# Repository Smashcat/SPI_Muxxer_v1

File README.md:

# SPI_Muxxer_v1
8 Port ISP/SPI development and debugging board using ESP8266.

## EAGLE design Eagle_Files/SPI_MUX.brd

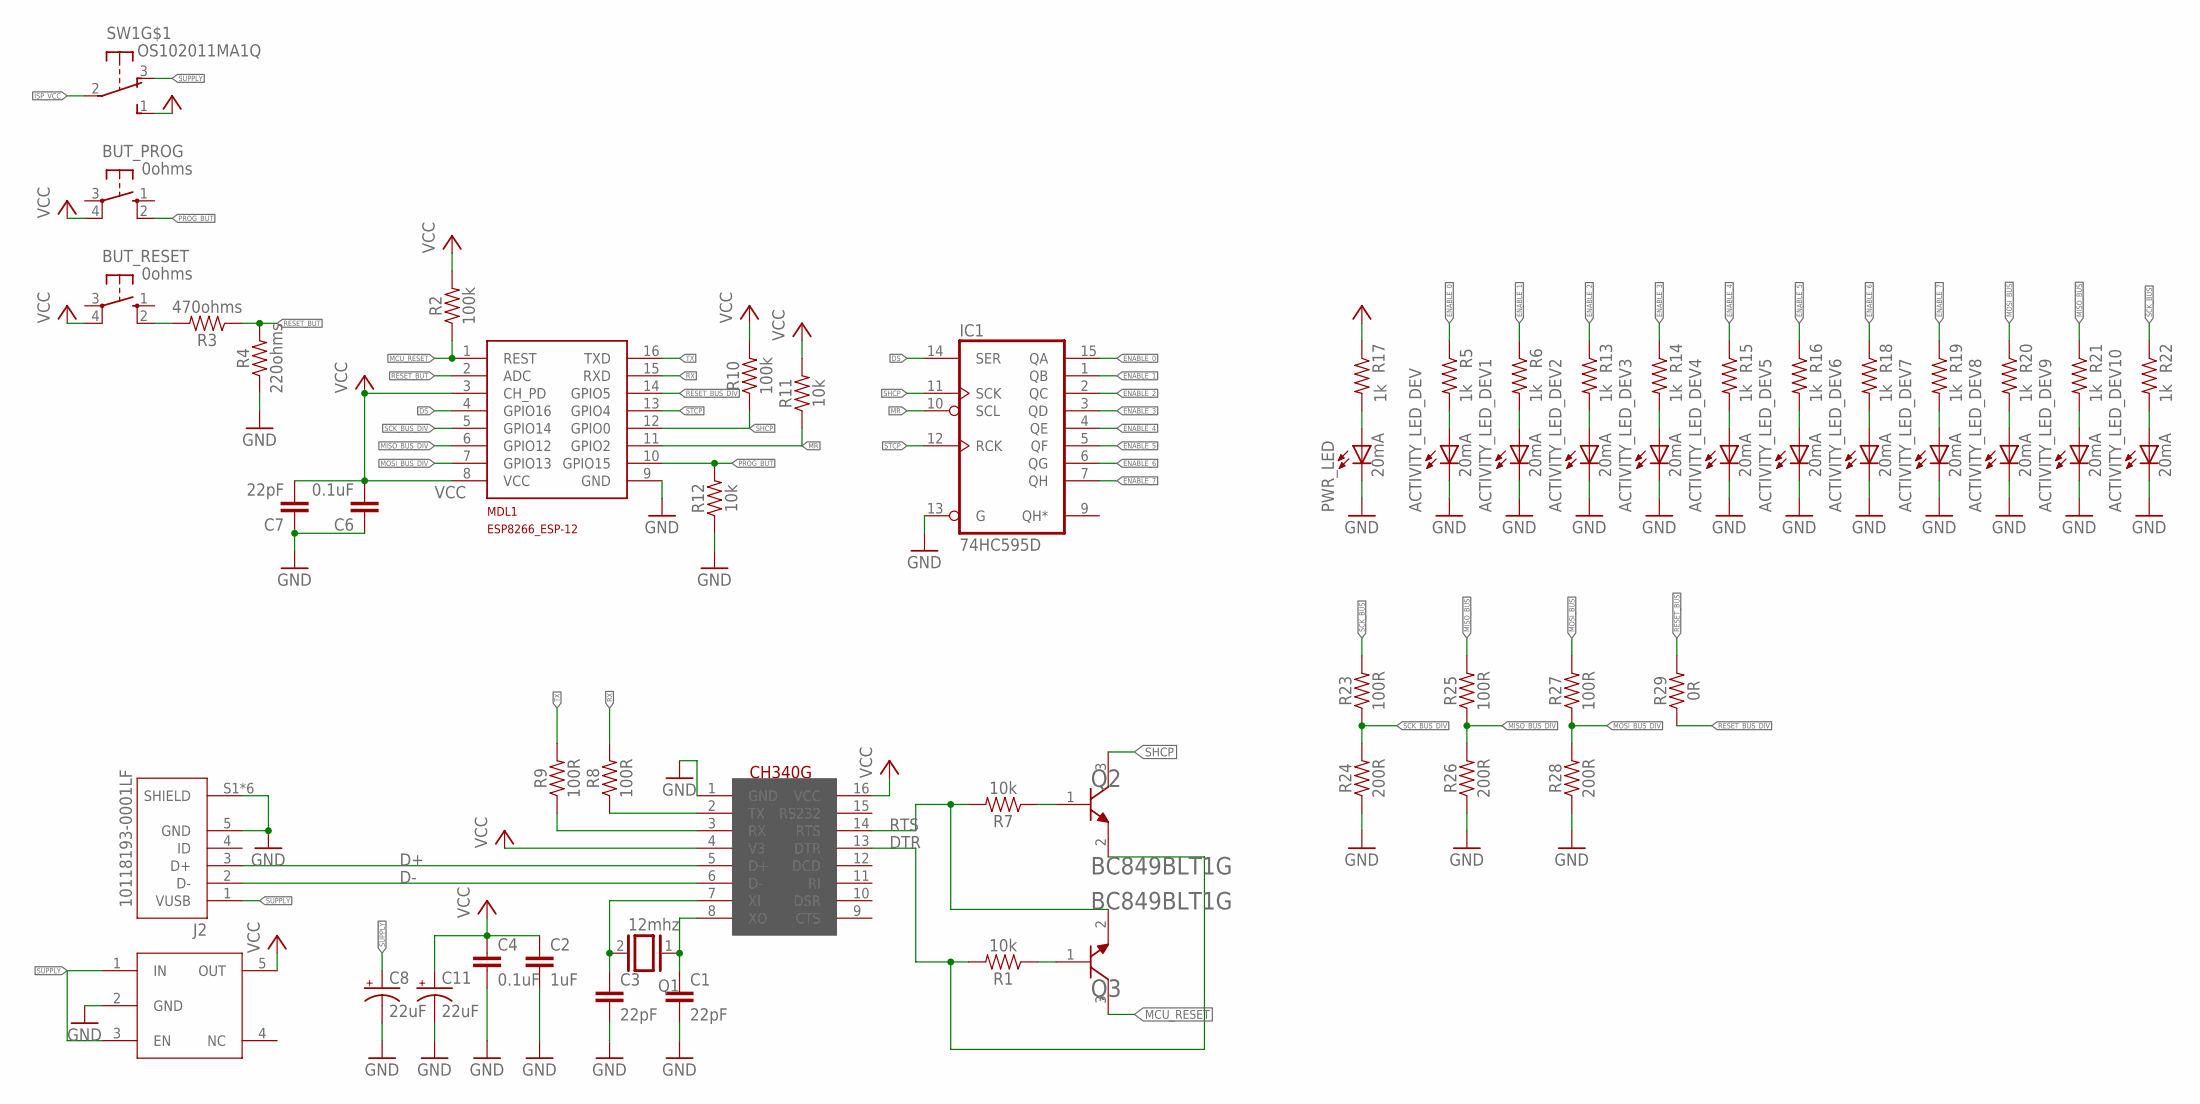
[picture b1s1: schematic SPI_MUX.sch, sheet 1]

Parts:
3V3_REGULATOR: 3v3 LDO; NCP718BSN330T1G
ACTIVITY_LED_DEV, ACTIVITY_LED_DEV1, ACTIVITY_LED_DEV2, ACTIVITY_LED_DEV3, ACTIVITY_LED_DEV4, ACTIVITY_LED_DEV5, ACTIVITY_LED_DEV6, ACTIVITY_LED_DEV7, ACTIVITY_LED_DEV8, ACTIVITY_LED_DEV9, ACTIVITY_LED_DEV10: 20mA; CHIP-LED0603
BUT_PROG: 0ohms; B3F-10XX
BUT_RESET: 0ohms; B3F-10XX
C1, C3, C7: 22pF; C0603
C2: 1uF; C0603
C4, C6: 0.1uF; C0603
C8, C11: 22uF; PANASONIC_C
IC1: 74HC595D; SO16
J2: 10118193-0001LF; FCI_10118193-0001LF
MDL1: MCU; ESP8266-ESP12
PWR_LED: 20mA; CHIP-LED0603
Q1: 12mhz; QS
Q2, Q3: ON_SEMICONDUCTOR_BC849BLT1GON_SEMICONDUCTOR_BC849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; ON_SEMICONDUCTOR_BC849BLT1G_0
R1, R7, R11, R12: 10k; 0603
R2, R10: 100k; 0603
R3: 470ohms; 0603
R4: 220ohms; 0603
R5, R6, R13, R14, R15, R16, R17, R18, R19, R20, R21, R22: 1k; 0603
R8, R9, R23, R25, R27: 100R; 0603
R24, R26, R28: 200R; 0603
R29: 0R; 0603
SW1: OS102011MA1Q
U$1: CH340G; SOIC16

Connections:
ACTIVITY: ACTIVITY_LED_DEV.A, R5.2
ACTIVITY1: ACTIVITY_LED_DEV1.A, R6.2
ACTIVITY2: ACTIVITY_LED_DEV2.A, R13.2
ACTIVITY3: ACTIVITY_LED_DEV3.A, R14.2
ACTIVITY4: ACTIVITY_LED_DEV4.A, R15.2
ACTIVITY5: ACTIVITY_LED_DEV5.A, R16.2
ACTIVITY6: ACTIVITY_LED_DEV6.A, R18.2
ACTIVITY7: ACTIVITY_LED_DEV7.A, R19.2
ACTIVITY8: ACTIVITY_LED_DEV8.A, R20.2
ACTIVITY9: ACTIVITY_LED_DEV9.A, R21.2
ACTIVITY10: ACTIVITY_LED_DEV10.A, R22.2
CRYSTALIN: C3.1, Q1.2, U$1.7 (XI)
CRYSTALOUT: C1.1, Q1.1, U$1.8 (XO)
D+: J2.3 (D+), U$1.5 (D+)
D-: J2.2 (D-), U$1.6 (D-)
DS: IC1.14 (SER), MDL1.4 (GPIO16)
DTR: Q2.2 (E), R1.2, U$1.13 (DTR)
ENABLE_0: IC1.15 (QA), R5.1; also elsewhere on the board
ENABLE_1: IC1.1 (QB), R6.1; also elsewhere on the board
ENABLE_2: IC1.2 (QC), R13.1; also elsewhere on the board
ENABLE_3: IC1.3 (QD), R14.1; also elsewhere on the board
ENABLE_4: IC1.4 (QE), R15.1; also elsewhere on the board
ENABLE_5: IC1.5 (QF), R16.1; also elsewhere on the board
ENABLE_6: IC1.6 (QG), R18.1; also elsewhere on the board
ENABLE_7: IC1.7 (QH), R19.1; also elsewhere on the board
GND: 3V3_REGULATOR.2 (GND), ACTIVITY_LED_DEV.C, ACTIVITY_LED_DEV1.C, ACTIVITY_LED_DEV2.C, ACTIVITY_LED_DEV3.C, ACTIVITY_LED_DEV4.C, ACTIVITY_LED_DEV5.C, ACTIVITY_LED_DEV6.C, ACTIVITY_LED_DEV7.C, ACTIVITY_LED_DEV8.C, ACTIVITY_LED_DEV9.C, ACTIVITY_LED_DEV10.C, C1.2, C2.2, C3.2, C4.2, C6.1, C7.1, C8.-, C11.-, IC1.8 (GND), IC1.13 (G), J2.5 (GND), J2.S1 (SHIELD), J2.S2 (SHIELD), J2.S3 (SHIELD), J2.S4 (SHIELD), J2.S5 (SHIELD), J2.S6 (SHIELD), MDL1.9 (GND), PWR_LED.C, R4.1, R12.1, R24.1, R26.1, R28.1, U$1.1 (GND); also elsewhere on the board
ISP_VCC: SW1.2; also elsewhere on the board
MCU_RESET: MDL1.1 (REST), Q3.3 (C), R2.1
MISO_BUS: R21.1, R25.2; also elsewhere on the board
MISO_BUS_DIV: MDL1.6 (GPIO12), R25.1, R26.2
MOSI_BUS: R20.1, R27.2; also elsewhere on the board
MOSI_BUS_DIV: MDL1.7 (GPIO13), R27.1, R28.2
MR: IC1.10 (SCL), MDL1.11 (GPIO2), R11.1
unnamed: BUT_RESET.2 (S1), R3.2
unnamed: Q3.1 (B), R1.1
unnamed: Q2.1 (B), R7.1
PROG_BUT: BUT_PROG.2 (S1), MDL1.10 (GPIO15), R12.2
PWR_RES: PWR_LED.A, R17.2
RESET_BUS: R29.2; also elsewhere on the board
RESET_BUS_DIV: MDL1.14 (GPIO5), R29.1
RESET_BUT: MDL1.2 (ADC), R3.1, R4.2
RTS: Q3.2 (E), R7.2, U$1.14 (RTS)
RX: MDL1.15 (RXD), R8.2
SCK_BUS: R22.1, R23.2; also elsewhere on the board
SCK_BUS_DIV: MDL1.5 (GPIO14), R23.1, R24.2
SHCP: IC1.11 (SCK), MDL1.12 (GPIO0), Q2.3 (C), R10.1
STCP: IC1.12 (RCK), MDL1.13 (GPIO4)
SUPPLY: 3V3_REGULATOR.1 (IN), 3V3_REGULATOR.3 (EN), C8.+, J2.1 (VUSB), SW1.3 (O)
TX: MDL1.16 (TXD), R9.2
TXFROMMCU: R9.1, U$1.3 (RX)
TXFROMPROGRAMMER: R8.1, U$1.2 (TX)
VCC: 3V3_REGULATOR.5 (OUT), BUT_PROG.4 (P1), BUT_RESET.4 (P1), C2.1, C4.1, C6.2, C7.2, C11.+, IC1.16 (VCC), MDL1.3 (CH_PD), MDL1.8 (VCC), R2.2, R10.2, R11.2, R17.1, SW1.1 (S), U$1.4 (V3), U$1.16 (VCC); also elsewhere on the board

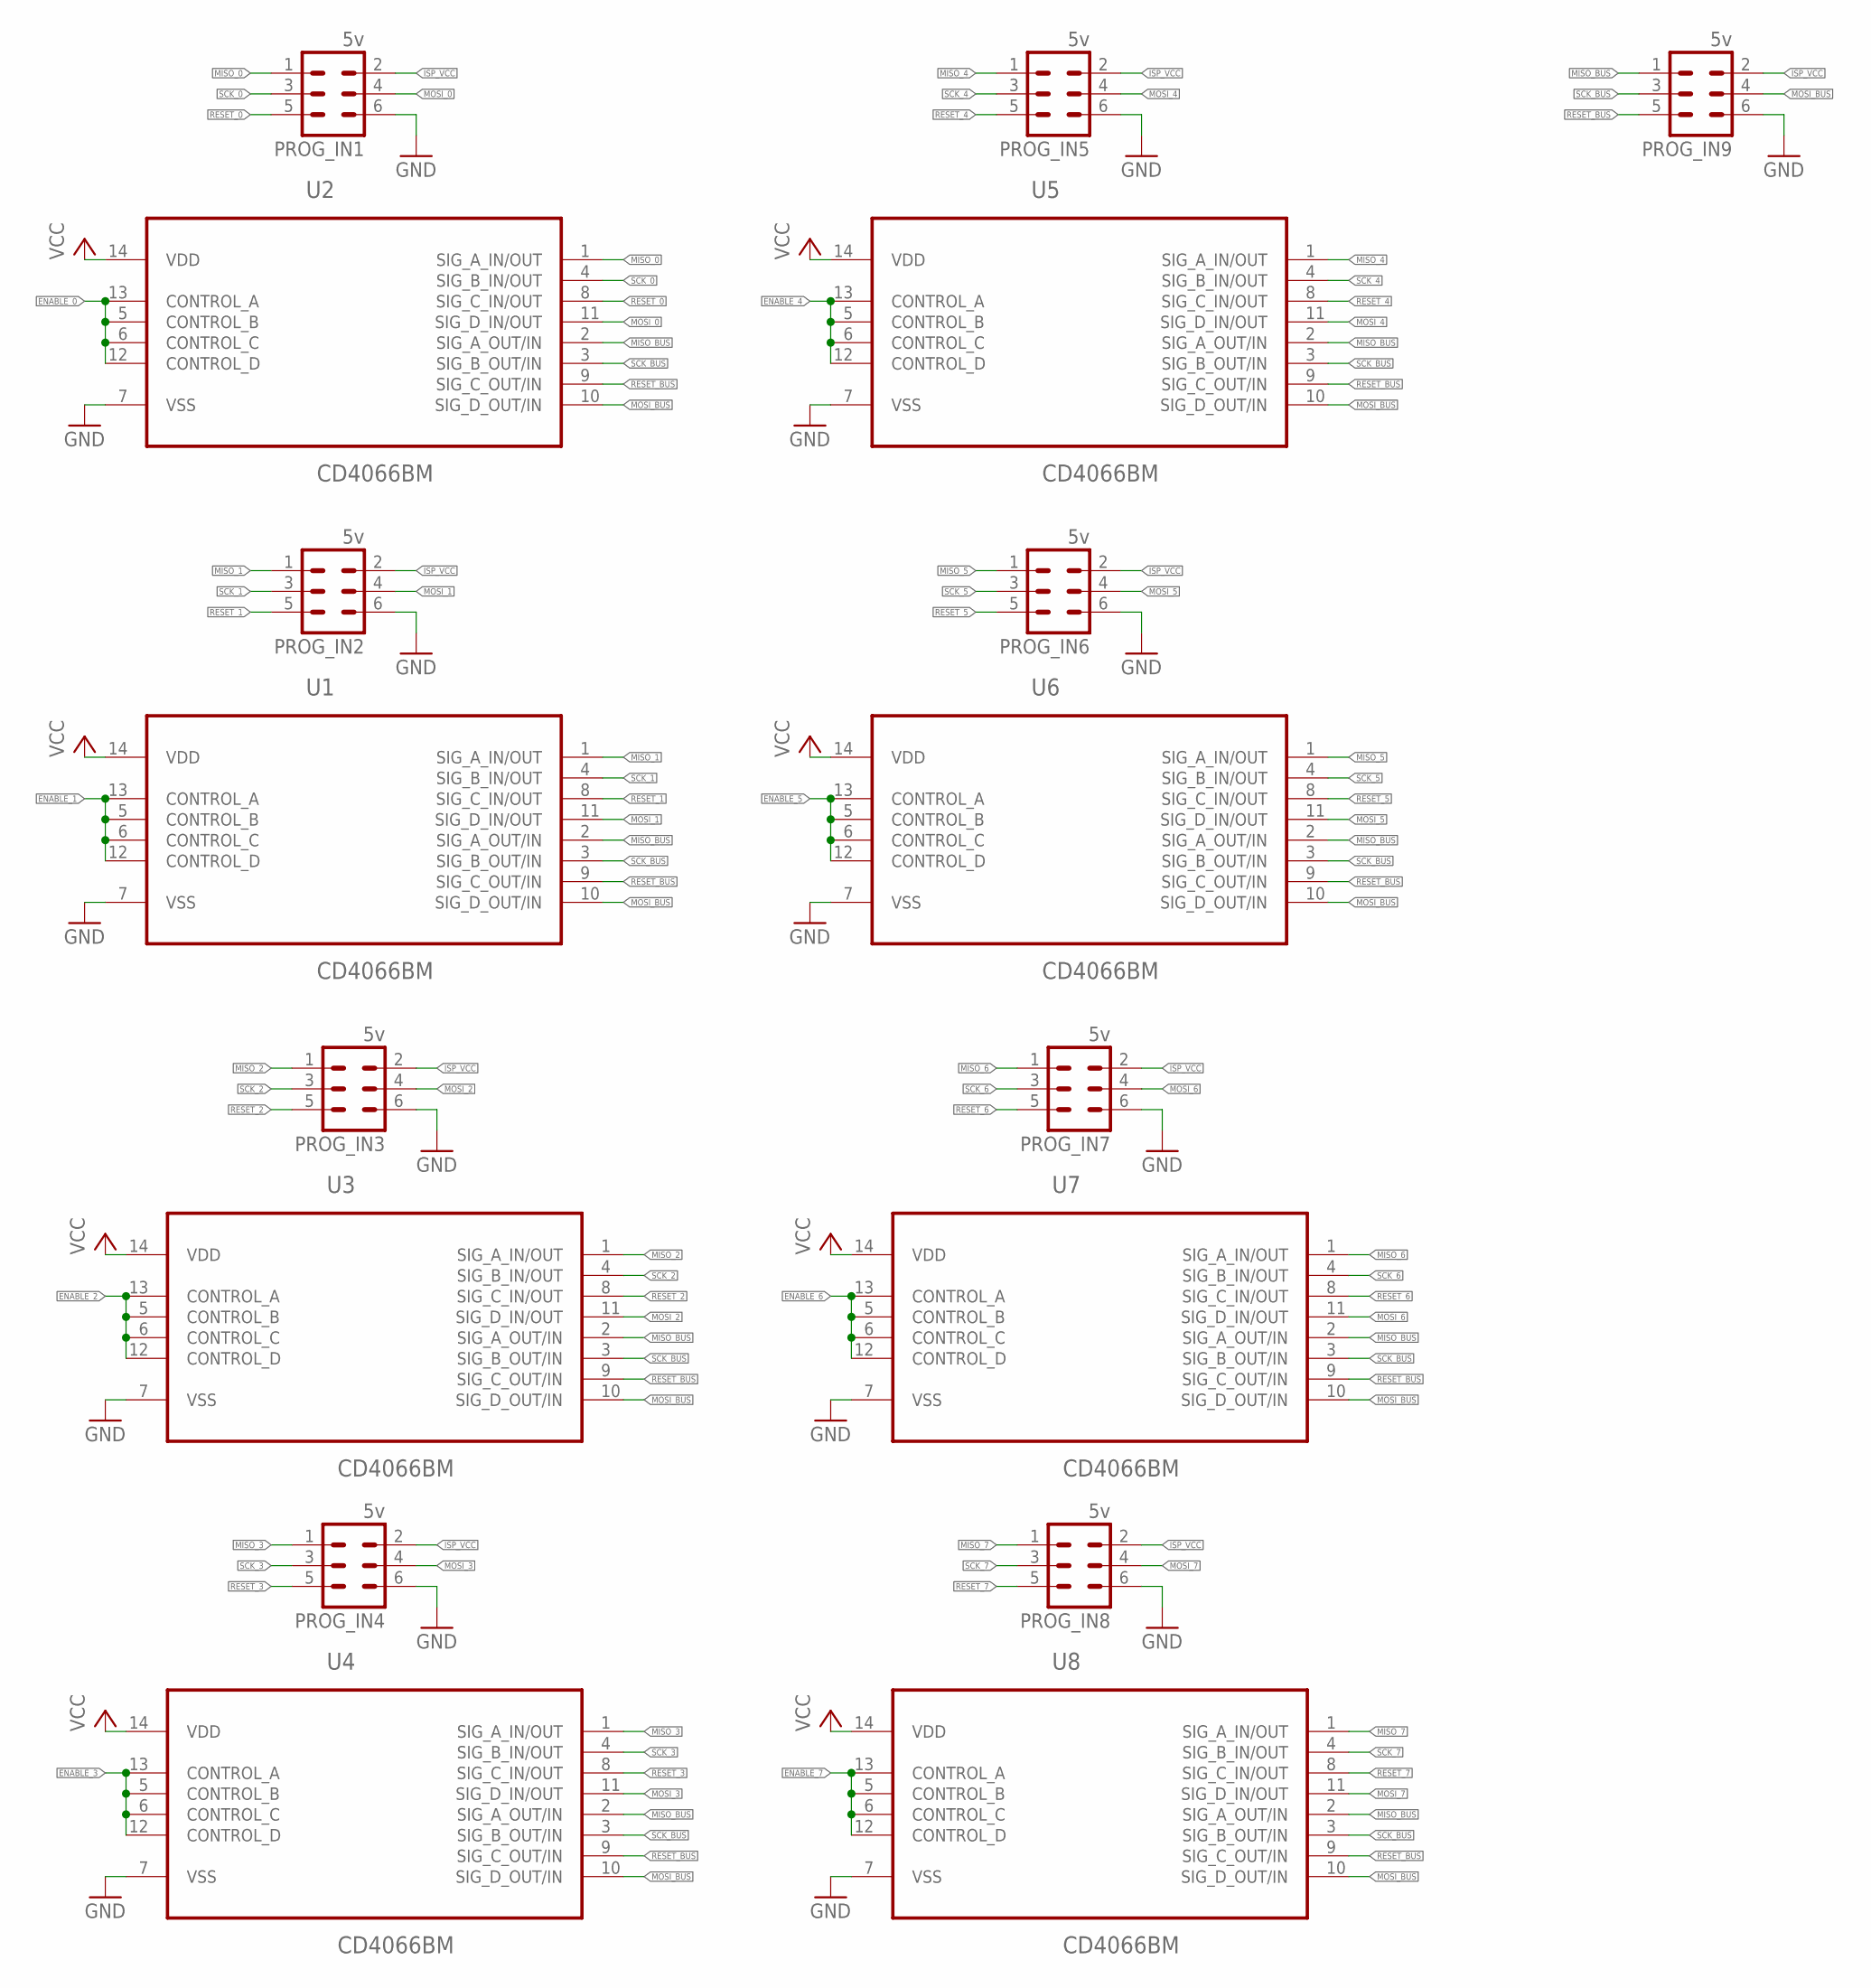
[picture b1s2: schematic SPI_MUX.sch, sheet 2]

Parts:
PROG_IN1, PROG_IN2, PROG_IN3, PROG_IN4, PROG_IN5, PROG_IN6, PROG_IN7, PROG_IN8, PROG_IN9: 5v; MA03-2
U1, U2, U3, U4, U5, U6, U7, U8: CD4066BM; SOIC127P600X175-14N

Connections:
ENABLE_0: U2.5 (CONTROL_B), U2.6 (CONTROL_C), U2.12 (CONTROL_D), U2.13 (CONTROL_A); also elsewhere on the board
ENABLE_1: U1.5 (CONTROL_B), U1.6 (CONTROL_C), U1.12 (CONTROL_D), U1.13 (CONTROL_A); also elsewhere on the board
ENABLE_2: U3.5 (CONTROL_B), U3.6 (CONTROL_C), U3.12 (CONTROL_D), U3.13 (CONTROL_A); also elsewhere on the board
ENABLE_3: U4.5 (CONTROL_B), U4.6 (CONTROL_C), U4.12 (CONTROL_D), U4.13 (CONTROL_A); also elsewhere on the board
ENABLE_4: U5.5 (CONTROL_B), U5.6 (CONTROL_C), U5.12 (CONTROL_D), U5.13 (CONTROL_A); also elsewhere on the board
ENABLE_5: U6.5 (CONTROL_B), U6.6 (CONTROL_C), U6.12 (CONTROL_D), U6.13 (CONTROL_A); also elsewhere on the board
ENABLE_6: U7.5 (CONTROL_B), U7.6 (CONTROL_C), U7.12 (CONTROL_D), U7.13 (CONTROL_A); also elsewhere on the board
ENABLE_7: U8.5 (CONTROL_B), U8.6 (CONTROL_C), U8.12 (CONTROL_D), U8.13 (CONTROL_A); also elsewhere on the board
GND: PROG_IN1.6, PROG_IN2.6, PROG_IN3.6, PROG_IN4.6, PROG_IN5.6, PROG_IN6.6, PROG_IN7.6, PROG_IN8.6, PROG_IN9.6, U1.7 (VSS), U2.7 (VSS), U3.7 (VSS), U4.7 (VSS), U5.7 (VSS), U6.7 (VSS), U7.7 (VSS), U8.7 (VSS); also elsewhere on the board
ISP_VCC: PROG_IN1.2, PROG_IN2.2, PROG_IN3.2, PROG_IN4.2, PROG_IN5.2, PROG_IN6.2, PROG_IN7.2, PROG_IN8.2, PROG_IN9.2; also elsewhere on the board
MISO_0: PROG_IN1.1, U2.1 (SIG_A_IN/OUT)
MISO_1: PROG_IN2.1, U1.1 (SIG_A_IN/OUT)
MISO_2: PROG_IN3.1, U3.1 (SIG_A_IN/OUT)
MISO_3: PROG_IN4.1, U4.1 (SIG_A_IN/OUT)
MISO_4: PROG_IN5.1, U5.1 (SIG_A_IN/OUT)
MISO_5: PROG_IN6.1, U6.1 (SIG_A_IN/OUT)
MISO_6: PROG_IN7.1, U7.1 (SIG_A_IN/OUT)
MISO_7: PROG_IN8.1, U8.1 (SIG_A_IN/OUT)
MISO_BUS: PROG_IN9.1, U1.2 (SIG_A_OUT/IN), U2.2 (SIG_A_OUT/IN), U3.2 (SIG_A_OUT/IN), U4.2 (SIG_A_OUT/IN), U5.2 (SIG_A_OUT/IN), U6.2 (SIG_A_OUT/IN), U7.2 (SIG_A_OUT/IN), U8.2 (SIG_A_OUT/IN); also elsewhere on the board
MOSI_0: PROG_IN1.4, U2.11 (SIG_D_IN/OUT)
MOSI_1: PROG_IN2.4, U1.11 (SIG_D_IN/OUT)
MOSI_2: PROG_IN3.4, U3.11 (SIG_D_IN/OUT)
MOSI_3: PROG_IN4.4, U4.11 (SIG_D_IN/OUT)
MOSI_4: PROG_IN5.4, U5.11 (SIG_D_IN/OUT)
MOSI_5: PROG_IN6.4, U6.11 (SIG_D_IN/OUT)
MOSI_6: PROG_IN7.4, U7.11 (SIG_D_IN/OUT)
MOSI_7: PROG_IN8.4, U8.11 (SIG_D_IN/OUT)
MOSI_BUS: PROG_IN9.4, U1.10 (SIG_D_OUT/IN), U2.10 (SIG_D_OUT/IN), U3.10 (SIG_D_OUT/IN), U4.10 (SIG_D_OUT/IN), U5.10 (SIG_D_OUT/IN), U6.10 (SIG_D_OUT/IN), U7.10 (SIG_D_OUT/IN), U8.10 (SIG_D_OUT/IN); also elsewhere on the board
RESET_0: PROG_IN1.5, U2.8 (SIG_C_IN/OUT)
RESET_1: PROG_IN2.5, U1.8 (SIG_C_IN/OUT)
RESET_2: PROG_IN3.5, U3.8 (SIG_C_IN/OUT)
RESET_3: PROG_IN4.5, U4.8 (SIG_C_IN/OUT)
RESET_4: PROG_IN5.5, U5.8 (SIG_C_IN/OUT)
RESET_5: PROG_IN6.5, U6.8 (SIG_C_IN/OUT)
RESET_6: PROG_IN7.5, U7.8 (SIG_C_IN/OUT)
RESET_7: PROG_IN8.5, U8.8 (SIG_C_IN/OUT)
RESET_BUS: PROG_IN9.5, U1.9 (SIG_C_OUT/IN), U2.9 (SIG_C_OUT/IN), U3.9 (SIG_C_OUT/IN), U4.9 (SIG_C_OUT/IN), U5.9 (SIG_C_OUT/IN), U6.9 (SIG_C_OUT/IN), U7.9 (SIG_C_OUT/IN), U8.9 (SIG_C_OUT/IN); also elsewhere on the board
SCK_0: PROG_IN1.3, U2.4 (SIG_B_IN/OUT)
SCK_1: PROG_IN2.3, U1.4 (SIG_B_IN/OUT)
SCK_2: PROG_IN3.3, U3.4 (SIG_B_IN/OUT)
SCK_3: PROG_IN4.3, U4.4 (SIG_B_IN/OUT)
SCK_4: PROG_IN5.3, U5.4 (SIG_B_IN/OUT)
SCK_5: PROG_IN6.3, U6.4 (SIG_B_IN/OUT)
SCK_6: PROG_IN7.3, U7.4 (SIG_B_IN/OUT)
SCK_7: PROG_IN8.3, U8.4 (SIG_B_IN/OUT)
SCK_BUS: PROG_IN9.3, U1.3 (SIG_B_OUT/IN), U2.3 (SIG_B_OUT/IN), U3.3 (SIG_B_OUT/IN), U4.3 (SIG_B_OUT/IN), U5.3 (SIG_B_OUT/IN), U6.3 (SIG_B_OUT/IN), U7.3 (SIG_B_OUT/IN), U8.3 (SIG_B_OUT/IN); also elsewhere on the board
VCC: U1.14 (VDD), U2.14 (VDD), U3.14 (VDD), U4.14 (VDD), U5.14 (VDD), U6.14 (VDD), U7.14 (VDD), U8.14 (VDD); also elsewhere on the board

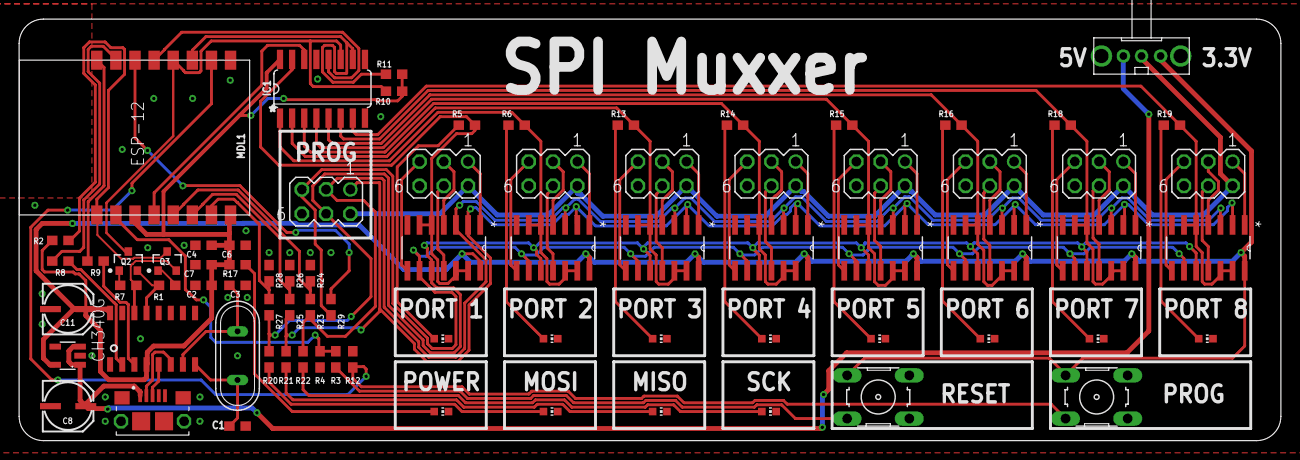
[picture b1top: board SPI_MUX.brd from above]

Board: 2 copper layers, 132.1 x 44.1 mm, 77 parts (0 on the bottom side), 84 nets.

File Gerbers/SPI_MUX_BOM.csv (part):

"Part";"Value";"Device";"Package";"Description";"AVAILABILITY";"CIIVA_IDS";"COMPONENT_LINK_1_DESCRIPTION";"COMPONENT_LINK_1_URL";"COMPONENT_LINK_3_DESCRIPTION";"COMPONENT_LINK_3_URL";"DATASHEET";"DATASHEET_VERSION";"DESCRIPTION";"FOOTPRINT_VARIANT_NAME_0";"FT_MIN_MHZ";"IC_CONTINUOUS_A";"IMPORTED";"IMPORTED_FROM";"IMPORT_TS";"MF";"MOUNTING_TECHNOLOGY";"MP";"MPN";"OC_FARNELL";"OC_NEWARK";"PACKAGE";"PACKAGE_DESCRIPTION";"PACKAGE_VERSION";"PACKING";"POLARITY";"PREFIX";"PRICE";"PROD_ID";"RELEASE_DATE";"ROHS";"SPICEPREFIX";"SUPPLIER";"VALUE";"VAULT_GUID";"VAULT_REVISION";
"3V3_REGULATOR";"3v3 LDO";"NCP718BSN330T1G";"NCP718BSN330T1G";"";"";"";"";"";"";"";"";"";"";"";"";"";"";"";"";"";"";"";"";"";"";"";"";"";"";"";"";"";"";"";"";"";"";"";"";"";
"ACTIVITY_LED_DEV";"20mA";"LEDCHIP-LED0603";"CHIP-LED0603";"LED";"";"";"";"";"";"";"";"";"";"";"";"";"";"";"";"";"";"";"";"";"";"";"";"";"";"";"";"";"";"";"";"";"";"";"";"";
"ACTIVITY_LED_DEV1";"20mA";"LEDCHIP-LED0603";"CHIP-LED0603";"LED";"";"";"";"";"";"";"";"";"";"";"";"";"";"";"";"";"";"";"";"";"";"";"";"";"";"";"";"";"";"";"";"";"";"";"";"";
"ACTIVITY_LED_DEV2";"20mA";"LEDCHIP-LED0603";"CHIP-LED0603";"LED";"";"";"";"";"";"";"";"";"";"";"";"";"";"";"";"";"";"";"";"";"";"";"";"";"";"";"";"";"";"";"";"";"";"";"";"";
"ACTIVITY_LED_DEV3";"20mA";"LEDCHIP-LED0603";"CHIP-LED0603";"LED";"";"";"";"";"";"";"";"";"";"";"";"";"";"";"";"";"";"";"";"";"";"";"";"";"";"";"";"";"";"";"";"";"";"";"";"";
"ACTIVITY_LED_DEV4";"20mA";"LEDCHIP-LED0603";"CHIP-LED0603";"LED";"";"";"";"";"";"";"";"";"";"";"";"";"";"";"";"";"";"";"";"";"";"";"";"";"";"";"";"";"";"";"";"";"";"";"";"";
"ACTIVITY_LED_DEV5";"20mA";"LEDCHIP-LED0603";"CHIP-LED0603";"LED";"";"";"";"";"";"";"";"";"";"";"";"";"";"";"";"";"";"";"";"";"";"";"";"";"";"";"";"";"";"";"";"";"";"";"";"";
"ACTIVITY_LED_DEV6";"20mA";"LEDCHIP-LED0603";"CHIP-LED0603";"LED";"";"";"";"";"";"";"";"";"";"";"";"";"";"";"";"";"";"";"";"";"";"";"";"";"";"";"";"";"";"";"";"";"";"";"";"";
"ACTIVITY_LED_DEV7";"20mA";"LEDCHIP-LED0603";"CHIP-LED0603";"LED";"";"";"";"";"";"";"";"";"";"";"";"";"";"";"";"";"";"";"";"";"";"";"";"";"";"";"";"";"";"";"";"";"";"";"";"";
"ACTIVITY_LED_DEV8";"20mA";"LEDCHIP-LED0603";"CHIP-LED0603";"LED";"";"";"";"";"";"";"";"";"";"";"";"";"";"";"";"";"";"";"";"";"";"";"";"";"";"";"";"";"";"";"";"";"";"";"";"";
"ACTIVITY_LED_DEV9";"20mA";"LEDCHIP-LED0603";"CHIP-LED0603";"LED";"";"";"";"";"";"";"";"";"";"";"";"";"";"";"";"";"";"";"";"";"";"";"";"";"";"";"";"";"";"";"";"";"";"";"";"";
"ACTIVITY_LED_DEV10";"20mA";"LEDCHIP-LED0603";"CHIP-LED0603";"LED";"";"";"";"";"";"";"";"";"";"";"";"";"";"";"";"";"";"";"";"";"";"";"";"";"";"";"";"";"";"";"";"";"";"";"";"";
"BUT_PROG";"0ohms";"10-XX";"B3F-10XX";"OMRON SWITCH";"";"";"";"";"";"";"";"";"";"";"";"";"";"";"";"";"";"";"B3F-1000";"176432";"36M3542";"";"";"";"";"";"";"";"";"";"";"";"";"";"";"";
"BUT_RESET";"0ohms";"10-XX";"B3F-10XX";"OMRON SWITCH";"";"";"";"";"";"";"";"";"";"";"";"";"";"";"";"";"";"";"B3F-1000";"176432";"36M3542";"";"";"";"";"";"";"";"";"";"";"";"";"";"";"";
"C1";"22pF";"C-EUC0603";"C0603";"CAPACITOR, European symbol";"";"";"";"";"";"";"";"";"";"";"";"";"";"";"";"";"";"";"";"";"";"";"";"";"";"";"";"";"";"";"";"C";"";"";"";"";
"C2";"1uF";"C-EUC0603";"C0603";"CAPACITOR, European symbol";"";"";"";"";"";"";"";"";"";"";"";"";"";"";"";"";"";"";"";"";"";"";"";"";"";"";"";"";"";"";"";"C";"";"";"";"";
"C3";"22pF";"C-EUC0603";"C0603";"CAPACITOR, European symbol";"";"";"";"";"";"";"";"";"";"";"";"";"";"";"";"";"";"";"";"";"";"";"";"";"";"";"";"";"";"";"";"C";"";"";"";"";
"C4";"0.1uF";"C-EUC0603";"C0603";"CAPACITOR, European symbol";"";"";"";"";"";"";"";"";"";"";"";"";"";"";"";"";"";"";"";"";"";"";"";"";"";"";"";"";"";"";"";"C";"";"";"";"";
"C6";"0.1uF";"C-EUC0603";"C0603";"CAPACITOR, European symbol";"";"";"";"";"";"";"";"";"";"";"";"";"";"";"";"";"";"";"";"";"";"";"";"";"";"";"";"";"";"";"";"C";"";"";"";"";
"C7";"22pF";"C-EUC0603";"C0603";"CAPACITOR, European symbol";"";"";"";"";"";"";"";"";"";"";"";"";"";"";"";"";"";"";"";"";"";"";"";"";"";"";"";"";"";"";"";"C";"";"";"";"";
"C8";"22uF";"22UF-POLAR-PANASONIC_C-35V-20%";"PANASONIC_C";"22µF polarized capacitors";"";"";"";"";"";"";"";"";"";"";"";"";"";"";"";"";"";"";"";"";"";"";"";"";"";"";"";"";"CAP-08618";"";"";"";"";"22uF";"";"";
"C11";"22uF";"22UF-POLAR-PANASONIC_C-35V-20%";"PANASONIC_C";"22µF polarized capacitors";"";"";"";"";"";"";"";"";"";"";"";"";"";"";"";"";"";"";"";"";"";"";"";"";"";"";"";"";"CAP-08618";"";"";"";"";"22uF";"";"";
"IC1";"74HC595D";"74HC595D";"SO16";"8-bit SHIFT REGISTER, output latch";"";"";"";"";"";"";"";"";"";"";"";"";"";"";"";"";"";"";"";"";"";"";"";"";"";"";"";"";"";"";"";"";"";"";"";"";
"J2";"10118193-0001LF";"10118193-0001LF";"FCI_10118193-0001LF";"Micro USB B Type Receptacle";"Unavailable";"";"";"";"";"";"";"";" Single Port 5 Contact Shielded SMT MICRO USB B-Type Receptacle ";"";"";"";"";"";"";"Amphenol FCI";"";"10118193-0001LF";"";"";"";"None";"";"";"";"";"";"None";"";"";"";"";"";"";"";"";
"MDL1";"MCU";"ESP8266-12GPIO04/05_CORRECTED";"ESP8266-ESP12";"Espressif ESP8266 ESP-12 Module with GPIO04 and GPIO05 corrected.";"";"";"";"";"";"";"";"";"";"";"";"";"";"";"";"";"";"";"";"";"";"";"";"";"";"";"";"";"";"";"";"";"";"";"";"";
"PROG_IN1";"5v";"MA03-2";"MA03-2";"PIN HEADER";"";"";"";"";"";"";"";"";"";"";"";"";"";"";"";"";"";"";"";"unknown";"unknown";"";"";"";"";"";"";"";"";"";"";"";"";"";"";"";
"PROG_IN2";"5v";"MA03-2";"MA03-2";"PIN HEADER";"";"";"";"";"";"";"";"";"";"";"";"";"";"";"";"";"";"";"";"unknown";"unknown";"";"";"";"";"";"";"";"";"";"";"";"";"";"";"";
"PROG_IN3";"5v";"MA03-2";"MA03-2";"PIN HEADER";"";"";"";"";"";"";"";"";"";"";"";"";"";"";"";"";"";"";"";"unknown";"unknown";"";"";"";"";"";"";"";"";"";"";"";"";"";"";"";
"PROG_IN4";"5v";"MA03-2";"MA03-2";"PIN HEADER";"";"";"";"";"";"";"";"";"";"";"";"";"";"";"";"";"";"";"";"unknown";"unknown";"";"";"";"";"";"";"";"";"";"";"";"";"";"";"";
"PROG_IN5";"5v";"MA03-2";"MA03-2";"PIN HEADER";"";"";"";"";"";"";"";"";"";"";"";"";"";"";"";"";"";"";"";"unknown";"unknown";"";"";"";"";"";"";"";"";"";"";"";"";"";"";"";
"PROG_IN6";"5v";"MA03-2";"MA03-2";"PIN HEADER";"";"";"";"";"";"";"";"";"";"";"";"";"";"";"";"";"";"";"";"unknown";"unknown";"";"";"";"";"";"";"";"";"";"";"";"";"";"";"";
"PROG_IN7";"5v";"MA03-2";"MA03-2";"PIN HEADER";"";"";"";"";"";"";"";"";"";"";"";"";"";"";"";"";"";"";"";"unknown";"unknown";"";"";"";"";"";"";"";"";"";"";"";"";"";"";"";
"PROG_IN8";"5v";"MA03-2";"MA03-2";"PIN HEADER";"";"";"";"";"";"";"";"";"";"";"";"";"";"";"";"";"";"";"";"unknown";"unknown";"";"";"";"";"";"";"";"";"";"";"";"";"";"";"";
"PROG_IN9";"5v";"MA03-2";"MA03-2";"PIN HEADER";"";"";"";"";"";"";"";"";"";"";"";"";"";"";"";"";"";"";"";"unknown";"unknown";"";"";"";"";"";"";"";"";"";"";"";"";"";"";"";
"PWR_LED";"20mA";"LEDCHIP-LED0603";"CHIP-LED0603";"LED";"";"";"";"";"";"";"";"";"";"";"";"";"";"";"";"";"";"";"";"";"";"";"";"";"";"";"";"";"";"";"";"";"";"";"";"";
"Q1";"12mhz";"XTAL/S";"QS";"CRYSTAL";"";"";"";"";"";"";"";"";"";"";"";"";"";"";"";"";"";"";"";"";"";"";"";"";"";"";"";"";"";"";"";"";"";"";"";"";
"Q2";"ON_SEMICONDUCTOR_BC849BLT1GON_SEMICONDUCTOR_BC849BLT1G_0_0";"ON_SEMICONDUCTOR_BC849BLT1GON_SEMICONDUCTOR_BC849BLT1G_0_0";"ON_SEMICONDUCTOR_BC849BLT1G_0";"ONSC-NPN-B1E2C3-3";"";"19369299";"Manufacturer URL";"http://www.onsemi.com/";"Package Specification";"http://www.onsemi.cn/pub_link/Collateral/318-08.PDF";"http://www.onsemi.cn/pub_link/Collateral/BC846ALT1-D.PDF";"Rev. 11";"";"Manufacturer Recommended";"100";"0.1";"yes";"vault";"1521843736";"On Semiconductor";"Surface Mount";"";"BC849BLT1G";"";"";"SOT-23-3-318-08";"3-Pin Small Outline Transistor, Body 2.92 x 1.3 mm, Pitch 0.95 mm";"Rev. AP, 11/2009";"Tape and Reel";"NPN";"Q";"";"";"1406898388";"Yes";"";"";"";"19D3C7D6-08FD-4A81-9BD4-62C7617130FB";"B4675A61-FAF7-4072-9C56-0A9635A35669";
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
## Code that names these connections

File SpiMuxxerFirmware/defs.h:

// Pin definitions

#define RESET_BUT A0
#define DS        16
#define BUS_SCK   14
#define BUS_MISO  12
#define BUS_MOSI  13
#define PROG_BUT  15
#define MR         2
#define SHCP       0
#define STCP       4
#define BUS_RESET  5

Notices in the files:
parts and their libraries:
SparkFun-Resistors: Licensing: Creative Commons ShareAlike 4.0 International - https://creativecommons.org/licenses/by-sa/4.0
